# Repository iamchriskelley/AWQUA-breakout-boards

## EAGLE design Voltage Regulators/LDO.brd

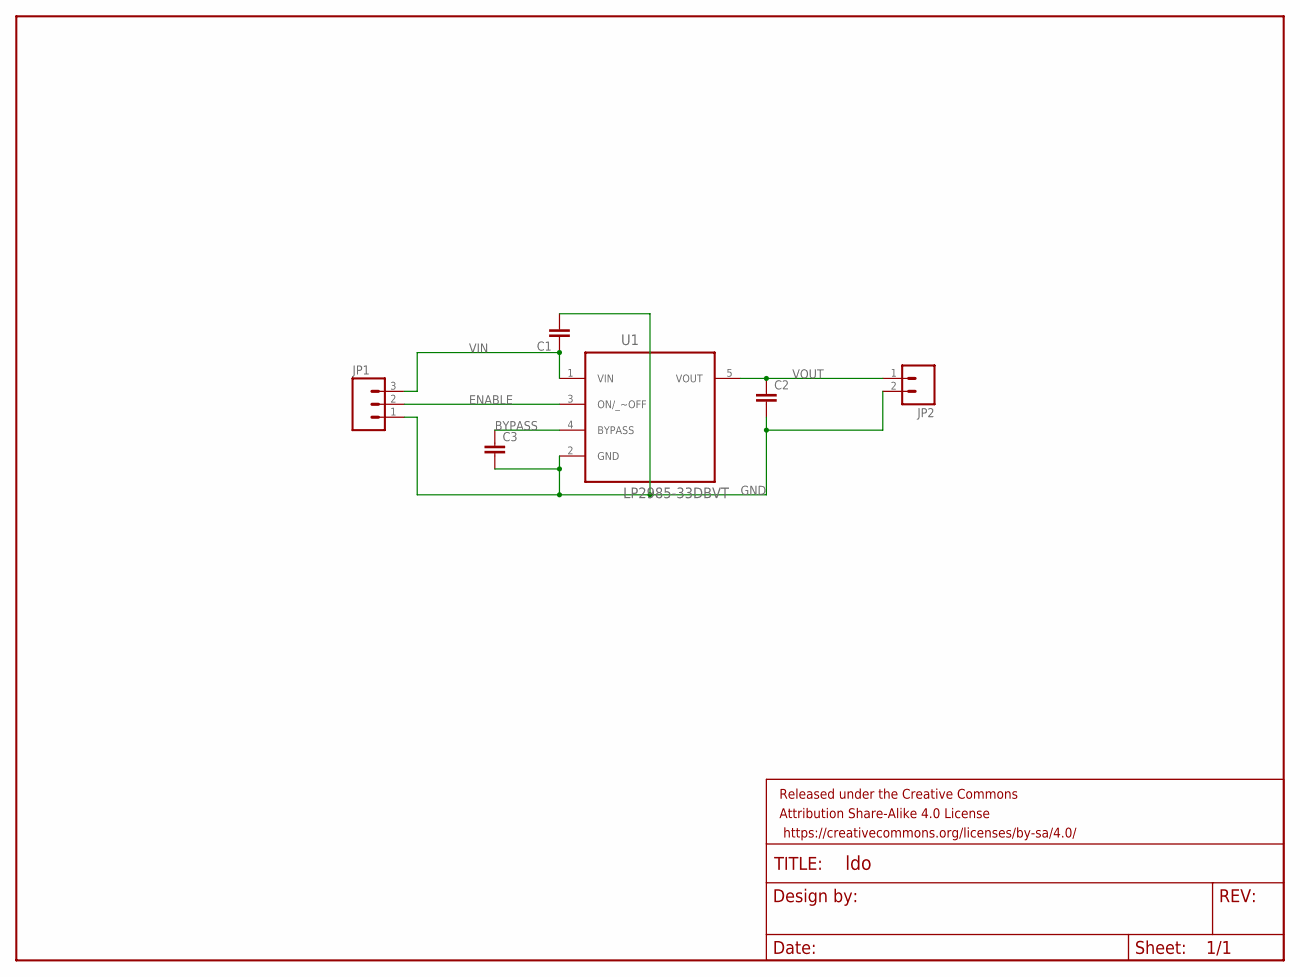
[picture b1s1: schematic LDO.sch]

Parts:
C1, C2, C3: CAP0603-CAP; 0603-CAP
FRAME1: FRAME-LETTER; CREATIVE_COMMONS
JP1: M03PTH; 1X03
JP2: M02PTH; 1X02
U1: LP2985-33DBVT; SOT95P280X145-5N

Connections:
BYPASS: C3.1, U1.4 (BYPASS)
ENABLE: JP1.2, U1.3 (ON/_~OFF)
GND: C1.2, C2.2, C3.2, JP1.1, JP2.2, U1.2 (GND)
VIN: C1.1, JP1.3, U1.1 (VIN)
VOUT: C2.1, JP2.1, U1.5 (VOUT)

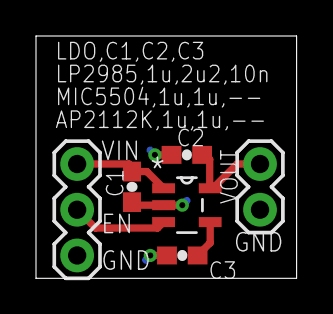
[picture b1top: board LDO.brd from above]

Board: 2 copper layers, 14.5 x 13.5 mm, 7 parts (0 on the bottom side), 5 nets.

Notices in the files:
parts and their libraries:
SparkFun-Passives: Licensing: Creative Commons ShareAlike 4.0 International - https://creativecommons.org/licenses/by-sa/4.0
SparkFun-Aesthetics: Released under the Creative Commons Attribution Share-Alike 4.0 License
SparkFun-Aesthetics: https://creativecommons.org/licenses/by-sa/4.0
